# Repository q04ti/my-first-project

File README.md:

# Starbie

Starbie is a small, motion-controlled digital pet for a desk. The idea is pretty simple: build a compact little companion with a tiny display, sensors, buttons, and a custom PCB, then let the user interact with it through movement, environmental readings, and physical input.

This is my Week 1 Starbie build, made from scratch. The KiCad schematic and custom carrier PCB are complete, while hardware assembly and testing are still ahead. The firmware source is included too, but right now it's a hardware-independent foundation with the sensor, display, and pet-behavior code marked for implementation after hardware bring-up.

## How It Works

The XIAO ESP32-C3 is the main microcontroller. It handles the 3.3 V logic and reads the sensors and buttons, while the OLED is meant to show Starbie's face and future state information. Basically, it's the part that ties everything together.

| Component | Connection | Role |
| --- | --- | --- |
| J1 — Seeed Studio XIAO ESP32-C3 | Main controller | Processes inputs and drives the project |
| J2 — 0.96-inch 128x64 4-pin I2C OLED | SDA → D4 / GPIO6; SCL → D5 / GPIO7; 3V3; GND | Display for Starbie's face and planned information |
| J3 — MPU6050 | SDA → D4 / GPIO6; SCL → D5 / GPIO7; 3V3; GND | Motion sensing |
| U1 — DHT11 | DHT11 data → D1 / GPIO3; 3V3; GND | Temperature and humidity sensing |
| SW1 | Button 1 → D2 / GPIO4; active-low input to GND | Physical user input |
| SW2 | Button 2 → D3 / GPIO5; active-low input to GND | Physical user input |
| R1 — 10 kΩ resistor | DHT11 data circuit | Pull-up resistor used with the DHT11 data connection |

The main signal flow is pretty straightforward:

```text
MPU6050 detects movement
        ↓
XIAO ESP32-C3 processes the input
        ↓
OLED can display Starbie's state
```

The DHT11 sends temperature and humidity readings to the XIAO, which can then pass information to the OLED. The buttons provide physical input to the XIAO too. The responses are still planned for now: the firmware has the pin definitions and program structure, but its display, sensor-reading, pet-state, menu, and animation functions still contain TODOs and haven't been tested on assembled hardware.

## Hardware and Design

The schematic was designed in KiCad, and the PCB was designed as a custom Starbie carrier PCB. The board has been routed, with 0 unrouted connections reported during the KiCad design check. DRC was run, and the actual electrical errors and unconnected items were resolved.

These are the design files:

- [KiCad project](hardware/kicad/Starbie.kicad_pro)
- [KiCad schematic](hardware/kicad/Starbie.kicad_sch)
- [PCB layout](hardware/kicad/Starbie.kicad_pcb)

Manufacturing outputs are included in [hardware/manufacturing/gerbers/](hardware/manufacturing/gerbers/), including the Gerber layers, Gerber job file, and both drill files. The physical PCB isn't assembled or tested yet.

## Photos & Screenshots

### PCB layout

*Completed Starbie PCB layout screenshot — this is what the finished board layout looks like right now.*

### Schematic

**Schematic screenshot:** Not available in the repository yet. The source schematic is available at [hardware/kicad/Starbie.kicad_sch](hardware/kicad/Starbie.kicad_sch), and a screenshot can be added here later.

### 3D model

**3D PCB render:** Not available in the repository yet. The source PCB is available at [hardware/kicad/Starbie.kicad_pcb](hardware/kicad/Starbie.kicad_pcb), so this section can get a render once one is available.

### Physical build

**Physical build:** Not assembled yet. This section will get real photos once the PCB and components are available.

## Wiring

Starbie uses a custom PCB, so the main component connections are captured in the KiCad schematic and PCB instead of being a loose hand-wired breadboard project.

No separate hand-wired wiring diagram is required for the current build; the electrical connections are documented in the [KiCad schematic](hardware/kicad/Starbie.kicad_sch) and [PCB layout](hardware/kicad/Starbie.kicad_pcb). The board does the wiring work here.

## Bill of Materials

Prices and links below come directly from [hardware/BOM/BOM.csv](hardware/BOM/BOM.csv). The PCB fabrication price is still `TBD` because the project doesn't specify a board house, order quantity, options, or shipping quote.

| Part | Qty | Purpose | Vendor | Price | Link |
| --- | ---: | --- | --- | ---: | --- |
| J1 — XIAO ESP32-C3 | 1 | Main microcontroller and USB-C board | Seeed Studio | $5.99 | [Product page](https://www.seeedstudio.com/Seeed-Studio-XIAO-ESP32C3-Pre-Soldered-p-6331.html) |
| J2 — 0.96-inch 128x64 OLED | 1 | I2C display / Starbie's face | Adafruit | $17.50 | [Product 326](https://www.adafruit.com/product/326) |
| J3 — MPU6050 breakout | 1 | Accelerometer and gyroscope | Adafruit | $12.95 | [Product 3886](https://www.adafruit.com/product/3886) |
| U1 — DHT11 module | 1 | Temperature and humidity sensing | DFRobot | $4.20 | [DFR0067](https://www.dfrobot.com/product-174.html) |
| SW1 — Omron B3F-1000 | 1 | Button 1 input | Omron | $0.35 | [Digi-Key listing](https://www.digikey.com/en/products/detail/aratas-formerly-omron-components/B3F-1000/33150) |
| SW2 — Omron B3F-1000 | 1 | Button 2 input | Omron | $0.35 | [Digi-Key listing](https://www.digikey.com/en/products/detail/aratas-formerly-omron-components/B3F-1000/33150) |
| R1 — 10 kΩ axial resistor | 1 | DHT11 data-circuit pull-up | Yageo | $0.10 | [CFR-25JB-52-10K](https://octopart.com/part/yageo-group/CFR-25JB-52-10K) |
| PCB1 — Custom Starbie PCB | 1 | Routed carrier PCB | TBD | TBD | — |

The switch rows use the Omron B3F-1000 named in the schematic and BOM. The verified PCB footprint is `Button_Switch_THT:SW_TH_Tactile_Omron_B3F-10xx`. Keeping the part and footprint aligned matters a lot here — tiny switches are not magically interchangeable just because they both have two switch states.

## Repository Structure

```text
.
├── README.md
├── hardware/
│   ├── kicad/                         KiCad project, schematic, and PCB
│   ├── manufacturing/gerbers/         Gerbers, Gerber job, and drill files
│   └── BOM/BOM.csv                    Bill of materials and supplier links
├── firmware/Starbie/Starbie.ino       Firmware foundation
├── assets/pcb-art/                    Project image assets
├── docs/                              Hardware, pinout, and project documentation
└── research/                          Component research
```

## Build Status and Next Steps

- PCB design: completed
- PCB routing: completed
- DRC: checked; actual electrical errors and unconnected items resolved
- Manufacturing files: generated
- BOM: prepared; PCB fabrication price remains TBD
- Firmware source: included; hardware-dependent behavior is not implemented or tested yet
- Physical assembly and testing: still pending

Next up:

1. Order the components and PCB.
2. Assemble the hardware.
3. Flash and test the firmware.
4. Test the OLED, MPU6050, DHT11, and buttons.
5. Photograph the completed physical build.
6. Update this README with real build photos and test results once they exist.

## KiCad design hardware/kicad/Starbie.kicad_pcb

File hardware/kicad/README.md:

# KiCad design area

This directory will contain the KiCad project after the component variants and electrical requirements are verified.

The `schematic/`, `pcb/`, and `libraries/` directories are intentionally empty. No fake `.kicad_sch` or `.kicad_pcb` files are created.

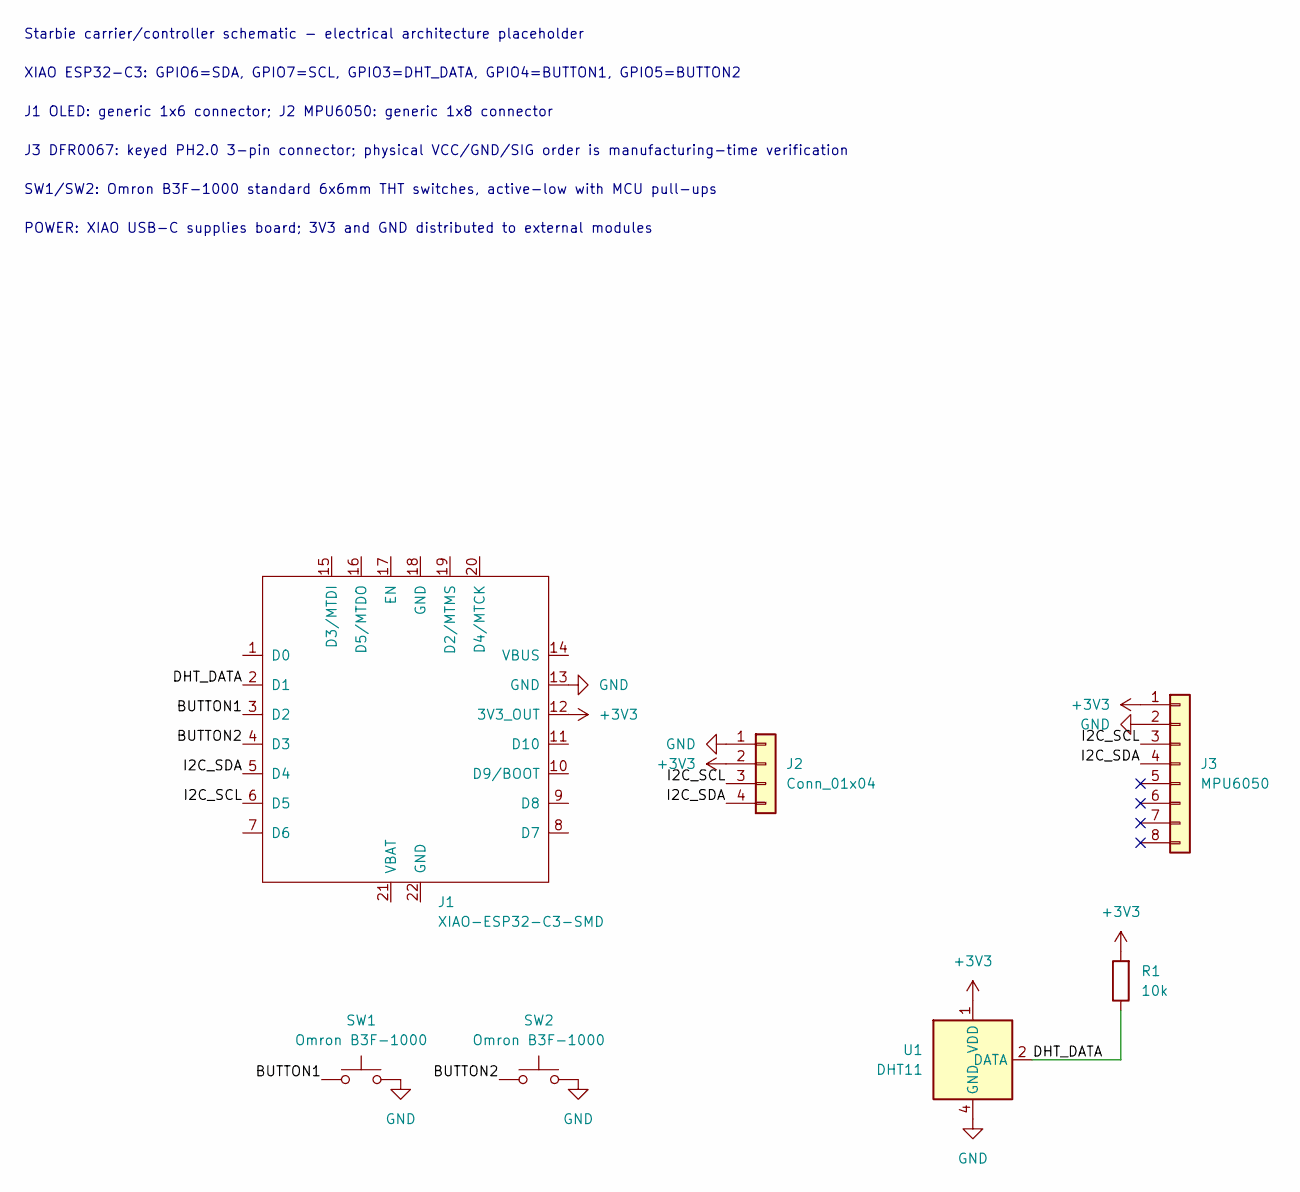
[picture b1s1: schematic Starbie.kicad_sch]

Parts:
J1: XIAO-ESP32-C3-SMD
J2: Conn_01x04; Display_128x64_096_I2C
J3: MPU6050; MPU6050_Module
R1: 10k; R_Axial_DIN0204_L3.6mm_D1.6mm_P7.62mm_Horizontal
SW1, SW2: Omron B3F-1000; SW_TH_Tactile_Omron_B3F-10xx
U1: DHT11; Aosong_DHT11_5.5x12.0_P2.54mm

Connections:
+3V3: J1.12, J2.2, J3.1, R1.2, U1.1 (VDD)
+5V: J1.14
/BUTTON1: J1.3, SW1.1
/BUTTON2: J1.4, SW2.1
/DHT_DATA: J1.2, R1.1, U1.2 (DATA)
/I2C_SCL: J1.6, J2.3, J3.3
/I2C_SDA: J1.5, J2.4, J3.4
GND: J1.13, J2.1, J3.2, SW1.2, SW2.2, U1.4 (GND)

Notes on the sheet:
Starbie carrier/controller schematic - electrical architecture placeholder
XIAO ESP32-C3: GPIO6=SDA, GPIO7=SCL, GPIO3=DHT_DATA, GPIO4=BUTTON1, GPIO5=BUTTON2
J1 OLED: generic 1x6 connector; J2 MPU6050: generic 1x8 connector
J3 DFR0067: keyed PH2.0 3-pin connector; physical VCC/GND/SIG order is manufacturing-time verification
SW1/SW2: Omron B3F-1000 standard 6x6mm THT switches, active-low with MCU pull-ups
POWER: XIAO USB-C supplies board; 3V3 and GND distributed to external modules

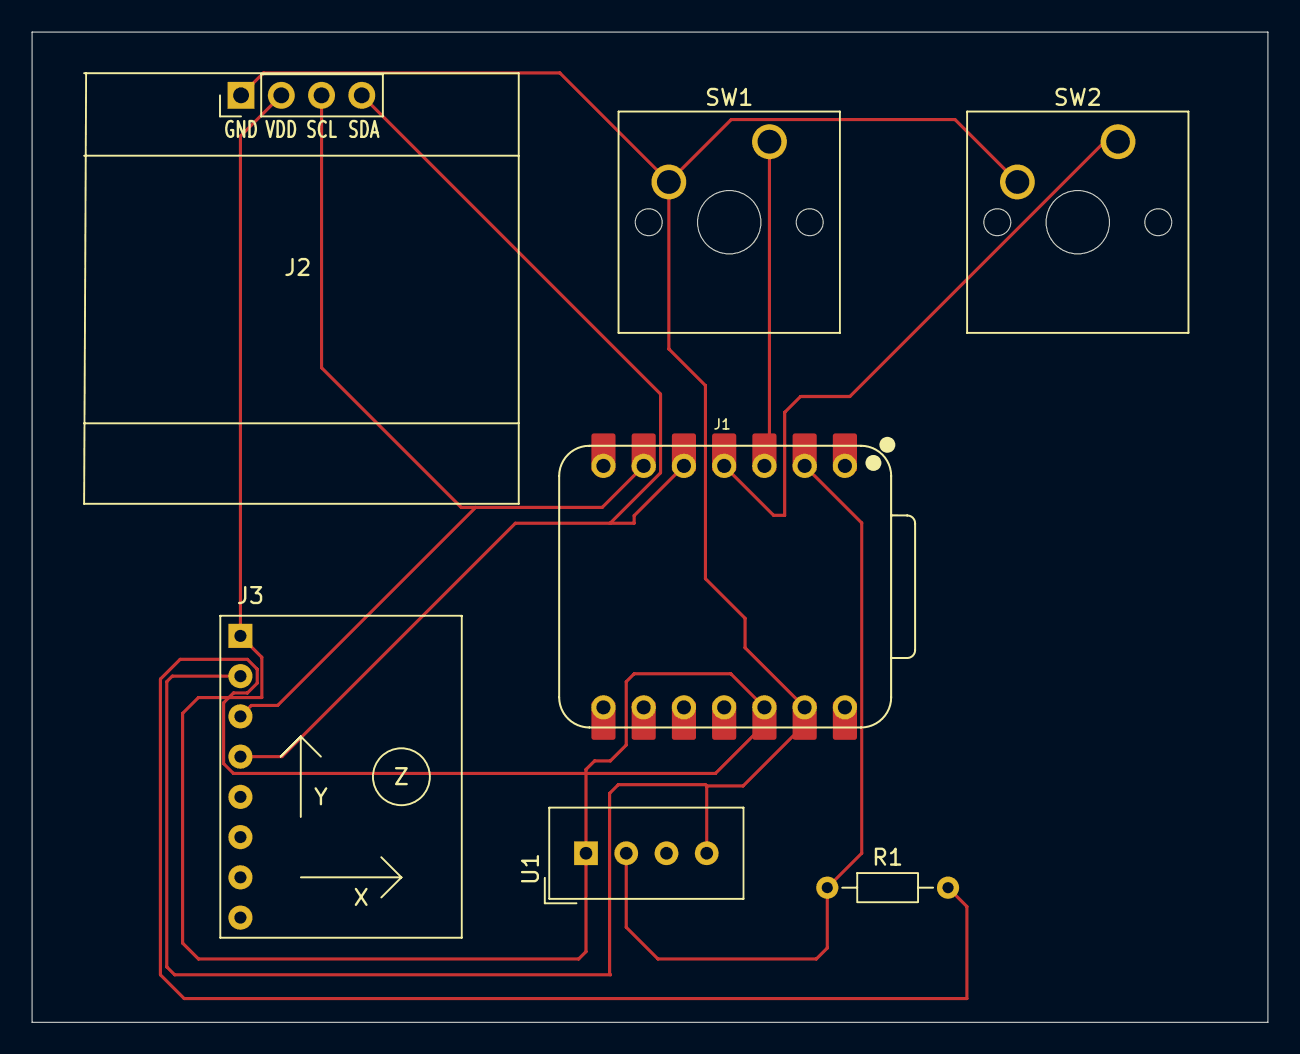
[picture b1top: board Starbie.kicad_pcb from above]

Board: 2 copper layers, 78.0 x 62.5 mm, 7 parts (0 on the bottom side), 7 nets.

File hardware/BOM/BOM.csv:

Reference,Component,Description,Quantity,Manufacturer,Part Number,Estimated Unit Cost,Estimated Total Cost,Source,Status,Notes
J1,Seeed Studio XIAO ESP32C3 pre-soldered,ESP32-C3 USB-C development board,1,Seeed Studio,SKU 6331 / 113991054,5.99,5.99,https://www.seeedstudio.com/Seeed-Studio-XIAO-ESP32C3-Pre-So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,Selected,PCB reference J1; source price is the documented observed single-unit price in USD
J2,Monochrome 0.96-inch 128x64 OLED breakout,SSD1306-family OLED configured for I2C,1,Adafruit,Product 326 current STEMMA-QT variant,17.50,17.50,https://www.adafruit.com/product/326,Selected,PCB reference J2; the completed PCB uses a four-pin OLED footprint, so verify the purchased board revision before assembly
J3,MPU-6050 6-DoF breakout,Accelerometer and gyroscope module,1,Adafruit,Product 3886,12.95,12.95,https://www.adafruit.com/product/3886,Selected,PCB reference J3; source price is the documented observed single-unit price in USD
U1,Gravity DHT11 Temperature and Humidity Sensor,3.3V to 5.5V DHT11 module,1,DFRobot,DFR0067,4.20,4.20,https://www.dfrobot.com/product-174.html,Selected,PCB reference U1; the completed PCB uses the DHT11 module footprint
SW1,Through-hole tactile push button,6x6 mm 4-pin SPST-NO switch,1,Omron,B3F-1000,0.35,0.35,https://www.digikey.com/en/products/detail/aratas-formerly-o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,Selected,PCB reference SW1; verified PCB footprint is Button_Switch_THT:SW_TH_Tactile_Omron_B3F-10xx
SW2,Through-hole tactile push button,6x6 mm 4-pin SPST-NO switch,1,Omron,B3F-1000,0.35,0.35,https://www.digikey.com/en/products/detail/aratas-formerly-o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,Selected,PCB reference SW2; verified PCB footprint is Button_Switch_THT:SW_TH_Tactile_Omron_B3F-10xx
R1,10k through-hole resistor,10k ohm axial resistor,1,Yageo,CFR-25JB-52-10K,0.10,0.10,https://octopart.com/part/yageo-group/CFR-25JB-52-10K,Selected,PCB reference R1; Octopart lists the Yageo 10k ohm 1/4 W axial through-hole resistor at 0.10 USD for one unit
PCB1,Custom Starbie carrier PCB,Completed routed Starbie PCB fabrication,1,TBD,TBD,TBD,TBD,TBD,Needs verification,Included as a fabrication line; no board house, order quantity, or reliable fabrication price is specified in the project
